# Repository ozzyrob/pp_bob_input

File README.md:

# pp_bob_input
 Beagleboneblack modular cnc cape system Input Board
 
To be used with pp_cape, converts 5v logic to 3v3 logic
  * Provides 8 Inputs Two can be used as for rotary encdoer either using hal_pru_generic or hal_arm335xQEP
  * Provides 5 Inputs one can be used for uart4 Rxd
  * Provides 4 Outputs one can be used for uart4 Txd

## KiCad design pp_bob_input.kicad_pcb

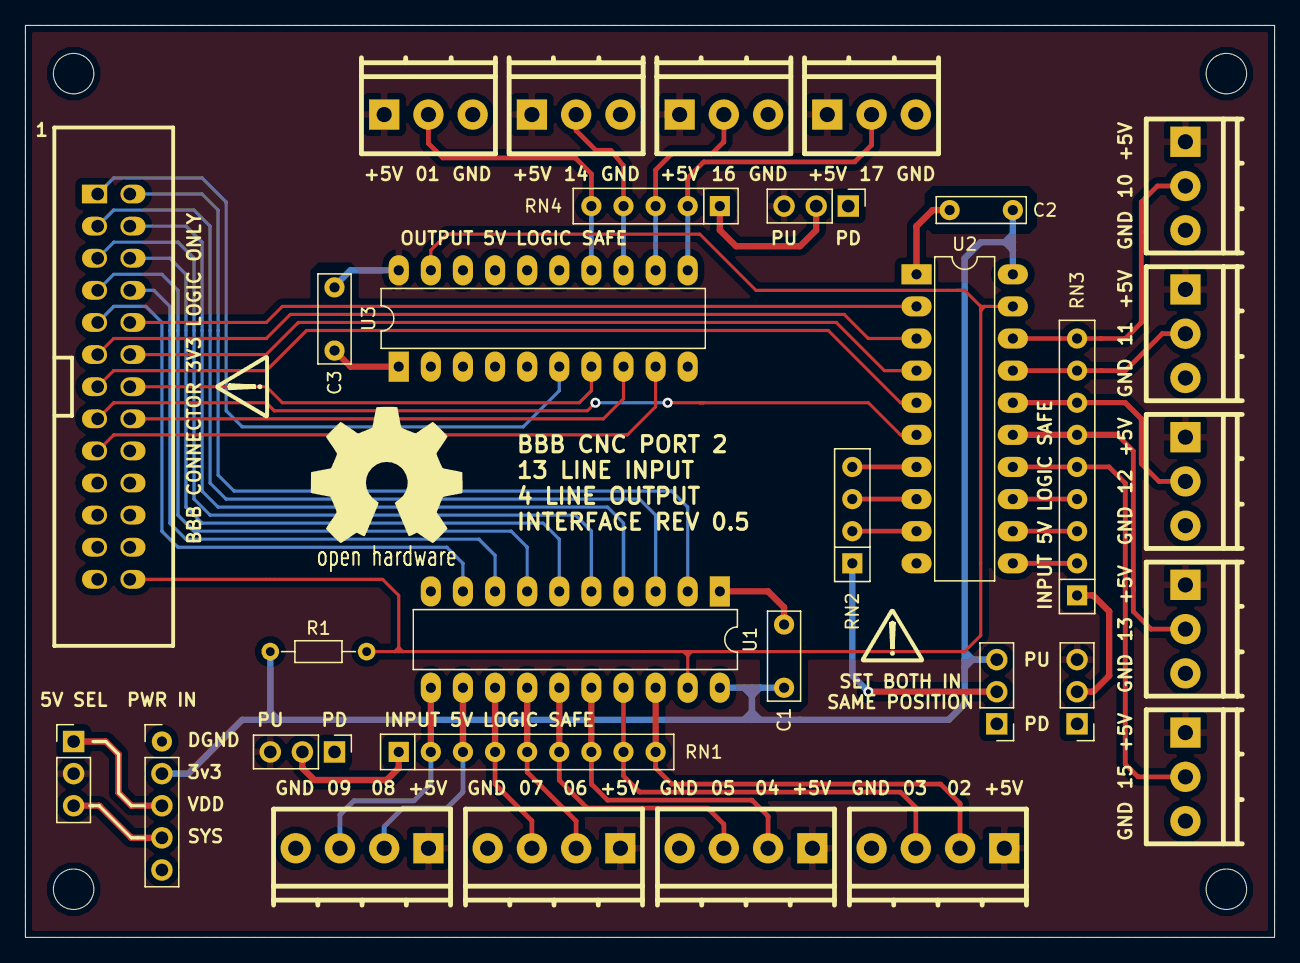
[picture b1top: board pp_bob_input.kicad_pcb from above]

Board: 2 copper layers, 98.8 x 72.1 mm, 31 parts (0 on the bottom side), 50 nets.

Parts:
C1, C3: 100n; C_Rect_L7.0mm_W2.5mm_P5.00mm
C2: 100n; C_Rect_L7.0mm_W2.0mm_P5.00mm
J_IN_1, J_IN_2, J_IN_3, J_IN_4: ST_1x04; pt_1,5-4-3,5-h
J_IN_5, J_IN_6, J_IN_7, J_IN_8, J_IN_9: ST_1x03; pt_1,5-3-3,5-h
J_OUT_5, J_OUT_6, J_OUT_7, J_OUT_8: ST_1x03; pt_1,5-3-3,5-h
P4: 13X2; vasch_strip_13x2
PWRIN_1: 1X5; Pin_Header_Straight_1x05_Pitch2.54mm
PWRSEL_1: 1X3; Pin_Header_Straight_1x03_Pitch2.54mm
R1: 4K7; R_Axial_DIN0204_L3.6mm_D1.6mm_P7.62mm_Horizontal
RN1, RN3: 4k7; R_Array_SIP9
RN2: 3k3; R_Array_SIP4
RN4: 4k7; R_Array_SIP5
SEL_1, SEL_2, SEL_3, SEL_4: 1X3; Pin_Header_Straight_1x03_Pitch2.54mm
U1, U2: 74LVC245; DIP-20_W7.62mm_LongPads
U3: 74LS541; DIP-20_W7.62mm_LongPads

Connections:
+3V3: C1.1, C2.1, PWRIN_1.2, R1.1, SEL_2.3, U1.20, U2.20
+5V: C3.2, J_IN_1.1, J_IN_2.1, J_IN_3.1, J_IN_4.1, J_IN_5.1, J_IN_6.1, J_IN_7.1, J_IN_8.1, J_IN_9.1, J_OUT_5.1, J_OUT_6.1, J_OUT_7.1, J_OUT_8.1, PWRSEL_1.2, SEL_1.3, SEL_3.3, SEL_4.3, U3.20
/IN-02: J_IN_1.2, RN1.9, U1.18
/IN-03: J_IN_1.3, RN1.8, U1.17
/IN-04: J_IN_2.2, RN1.7, U1.16
/IN-05: J_IN_2.3, RN1.6, U1.15
/IN-06: J_IN_3.2, RN1.5, U1.14
/IN-07: J_IN_3.3, RN1.4, U1.13
/IN-08: J_IN_4.2, RN1.3, U1.12
/IN-09: J_IN_4.3, RN1.2, U1.11
/IN-10: J_IN_5.2, RN3.9, U2.18
/IN-11: J_IN_6.2, RN3.8, U2.17
/IN-12: J_IN_7.2, RN3.7, U2.16
/IN-13: J_IN_8.2, RN3.6, U2.15
/IN-15: J_IN_9.2, RN3.5, U2.14
/OUT-01: J_OUT_5.2, RN4.5, U3.14
/OUT-14: J_OUT_6.2, RN4.4, U3.13
/OUT-16: J_OUT_7.2, RN4.3, U3.12
/OUT-17: J_OUT_8.2, RN4.2, U3.11
/SYS_+5v: PWRIN_1.3, PWRSEL_1.1
/VDD_+5v: PWRIN_1.4, PWRSEL_1.3
CHIP_ENABLE: P4.26, R1.2, U1.19, U2.19, U3.19
DB_01: P4.1, U3.6
DB_02: P4.2, U1.2
DB_03: P4.3, U1.3
DB_04: P4.4, U1.4
DB_05: P4.5, U1.5
DB_06: P4.6, U1.6
DB_07: P4.7, U1.7
DB_08: P4.8, U1.8
DB_09: P4.9, U1.9
DB_10: P4.10, U2.2
DB_11: P4.11, U2.3
DB_12: P4.12, U2.4
DB_13: P4.13, U2.5
DB_14: P4.14, U3.7
DB_15: P4.15, U2.6
DB_16: P4.16, U3.8
DB_17: P4.17, U3.9
GND: C1.2, C2.2, C3.1, J_IN_1.4, J_IN_2.4, J_IN_3.4, J_IN_4.4, J_IN_5.3, J_IN_6.3, J_IN_7.3, J_IN_8.3, J_IN_9.3, J_OUT_5.3, J_OUT_6.3, J_OUT_7.3, J_OUT_8.3, P4.18, P4.19, P4.20, P4.21, P4.22, P4.23, P4.24, P4.25, PWRIN_1.1, SEL_1.1, SEL_2.1, SEL_3.1, SEL_4.1, U1.1, U1.10, U2.1, U2.10, U3.1, U3.2, U3.3, U3.4, U3.5, U3.10
unnamed: RN1.1, SEL_1.2
unnamed: RN2.1, SEL_2.2
unnamed: RN2.2, U2.9
unnamed: RN2.3, U2.8
unnamed: RN2.4, U2.7
unnamed: RN3.1, SEL_3.2
unnamed: RN3.2, U2.11
unnamed: RN3.3, U2.12
unnamed: RN3.4, U2.13
unnamed: RN4.1, SEL_4.2

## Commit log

2017-04-13 Commit V0.2
2017-04-13 Redraw layout
2017-04-13 Schematic still to update, PCB about 95% done
2017-04-14 Initial V0.3 commit
2017-04-14 Clean up in line with pp_bob_output_v0.3
2017-04-24 Layout modded to max output board
2017-04-24 File centres.txt added
2017-04-25 Move DB_02 to DB_09 to front & DB_01,14,16,17 to rear.
2017-07-17 Add preproduction jpeg
2017-09-20 Fix silkscreen
2017-09-20 Add schematic
2017-09-20 Create Master file
2017-09-20 Add .gitattribute
